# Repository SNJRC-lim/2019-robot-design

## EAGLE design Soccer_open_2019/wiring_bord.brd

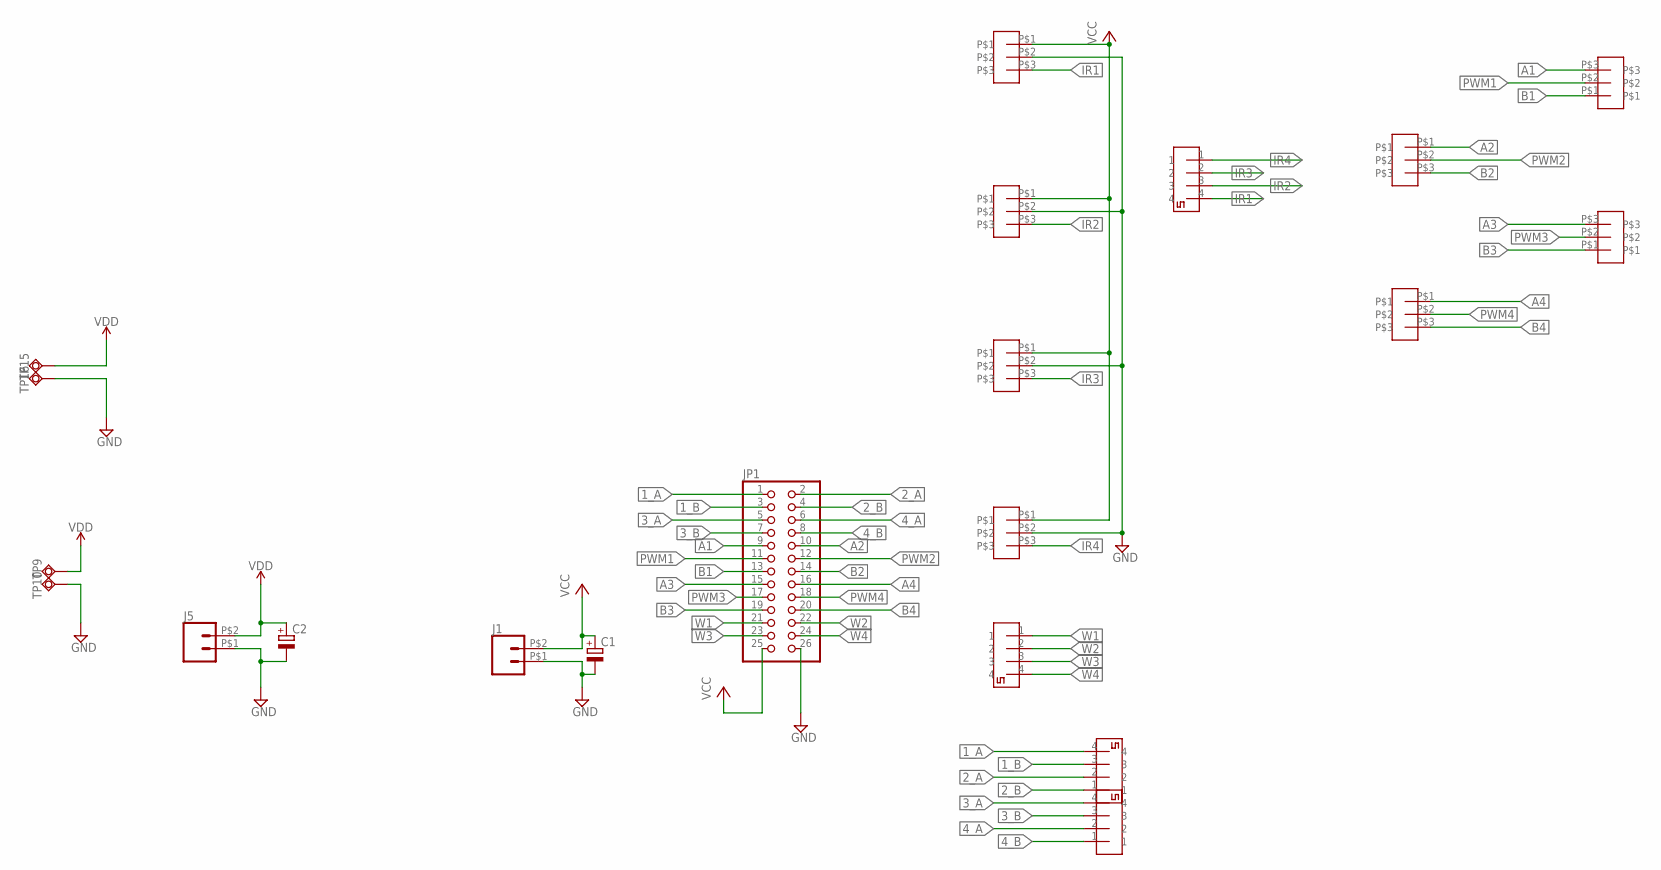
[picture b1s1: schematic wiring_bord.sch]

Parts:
C1, C2: CPOL-EUE2-5; E2-5
CONNECTOR1, CONNECTOR2, CONNECTOR3, CONNECTOR4: 2PIN
IR_DISTANCE1, IR_DISTANCE2, IR_DISTANCE3, IR_DISTANCE4, IR_DISTANCE5, IR_DISTANCE6, IR_DISTANCE7, IR_DISTANCE8: 3PIN
J1, J5: CONN_02PTH2; 1X02_BIG
JP1: PINHD-2X13; 2X13
TP9, TP10: TESTPAD_TPSQPAD1-20; TESTPAD_P1-20
TP15, TP16: TESTPAD_TPSQPAD1-13; TESTPAD_P1-13

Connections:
1_A: CONNECTOR3.4, JP1.1
1_B: CONNECTOR3.3, JP1.3
2_A: CONNECTOR3.2, JP1.2
2_B: CONNECTOR3.1, JP1.4
3_A: CONNECTOR4.4, JP1.5
3_B: CONNECTOR4.3, JP1.7
4_A: CONNECTOR4.2, JP1.6
4_B: CONNECTOR4.1, JP1.8
A1: IR_DISTANCE5.P$3, JP1.9
A2: IR_DISTANCE6.P$1, JP1.10
A3: IR_DISTANCE7.P$3, JP1.15
A4: IR_DISTANCE8.P$1, JP1.16
B1: IR_DISTANCE5.P$1, JP1.13
B2: IR_DISTANCE6.P$3, JP1.14
B3: IR_DISTANCE7.P$1, JP1.19
B4: IR_DISTANCE8.P$3, JP1.20
GND: C1.-, C2.-, IR_DISTANCE1.P$2, IR_DISTANCE2.P$2, IR_DISTANCE3.P$2, IR_DISTANCE4.P$2, J1.P$1 (1), J5.P$1 (1), JP1.26, TP10.TP, TP16.TP
IR1: CONNECTOR1.4, IR_DISTANCE1.P$3
IR2: CONNECTOR1.3, IR_DISTANCE2.P$3
IR3: CONNECTOR1.2, IR_DISTANCE3.P$3
IR4: CONNECTOR1.1, IR_DISTANCE4.P$3
PWM1: IR_DISTANCE5.P$2, JP1.11
PWM2: IR_DISTANCE6.P$2, JP1.12
PWM3: IR_DISTANCE7.P$2, JP1.17
PWM4: IR_DISTANCE8.P$2, JP1.18
VCC: C1.+, IR_DISTANCE1.P$1, IR_DISTANCE2.P$1, IR_DISTANCE3.P$1, IR_DISTANCE4.P$1, J1.P$2 (2), JP1.25
VDD: C2.+, J5.P$2 (2), TP9.TP, TP15.TP
W1: CONNECTOR2.1, JP1.21
W2: CONNECTOR2.2, JP1.22
W3: CONNECTOR2.3, JP1.23
W4: CONNECTOR2.4, JP1.24

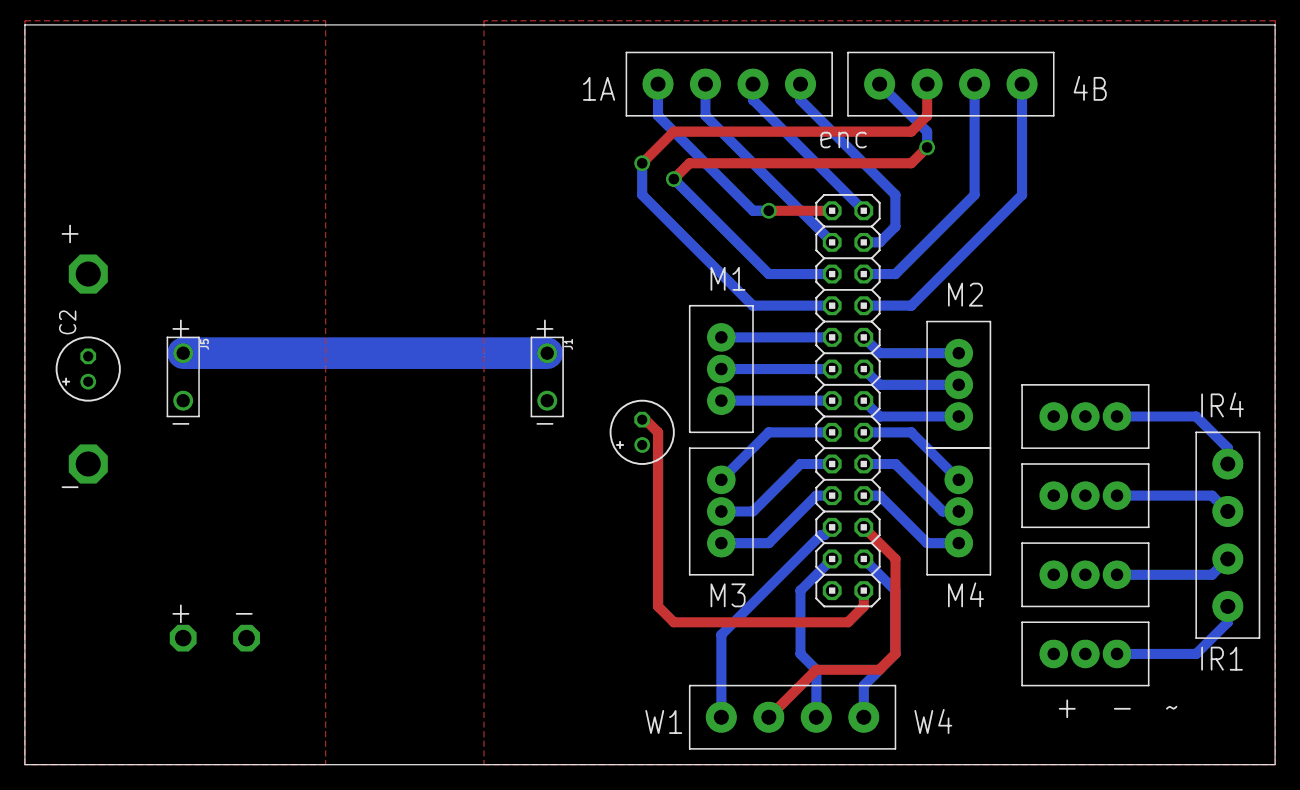
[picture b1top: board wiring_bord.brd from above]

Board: 2 copper layers, 100.3 x 59.4 mm, 21 parts (1 on the bottom side), 31 nets.

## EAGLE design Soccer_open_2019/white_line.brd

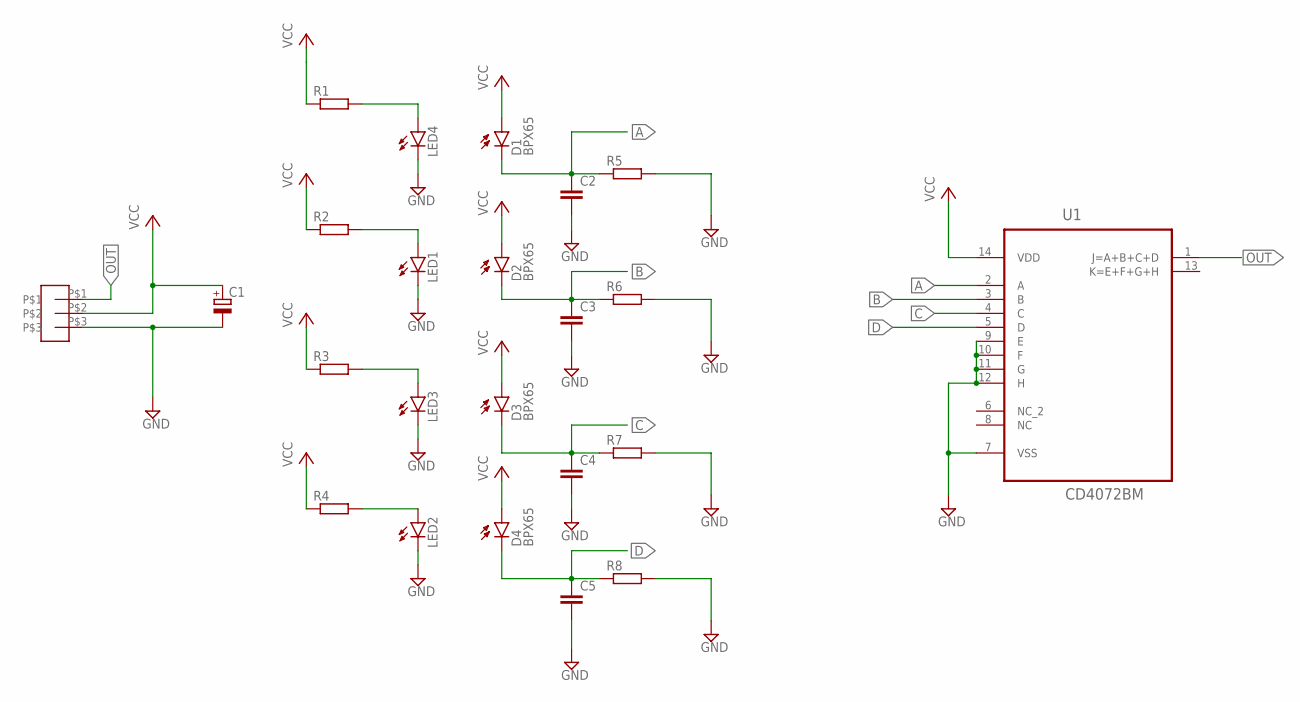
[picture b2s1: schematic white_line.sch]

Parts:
3PIN2: 3PIN
C1: CPOL-EUE2-5; E2-5
C2, C3, C4, C5: C-EU050-024X044; C050-024X044
D1, D2, D3, D4: BPX65
LED1, LED2, LED3, LED4: LED3MM
R1, R2, R3, R4, R5, R6, R7, R8: R-EU_0204/7; 0204/7
U1: CD4072BM; SOIC127P600X175-14N

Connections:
A: C2.1, D1.K (C), R5.1, U1.2 (A)
B: C3.1, D2.K (C), R6.1, U1.3 (B)
C: C4.1, D3.K (C), R7.1, U1.4 (C)
D: C5.1, D4.K (C), R8.1, U1.5 (D)
GND: 3PIN2.P$3, C1.-, C2.2, C3.2, C4.2, C5.2, LED1.K (C), LED2.K (C), LED3.K (C), LED4.K (C), R5.2, R6.2, R7.2, R8.2, U1.7 (VSS), U1.9 (E), U1.10 (F), U1.11 (G), U1.12 (H)
unnamed: LED4.A, R1.2
unnamed: LED1.A, R2.2
unnamed: LED3.A, R3.2
unnamed: LED2.A, R4.2
OUT: 3PIN2.P$1, U1.1 (J=A+B+C+D)
VCC: 3PIN2.P$2, C1.+, D1.A, D2.A, D3.A, D4.A, R1.1, R2.1, R3.1, R4.1, U1.14 (VDD)

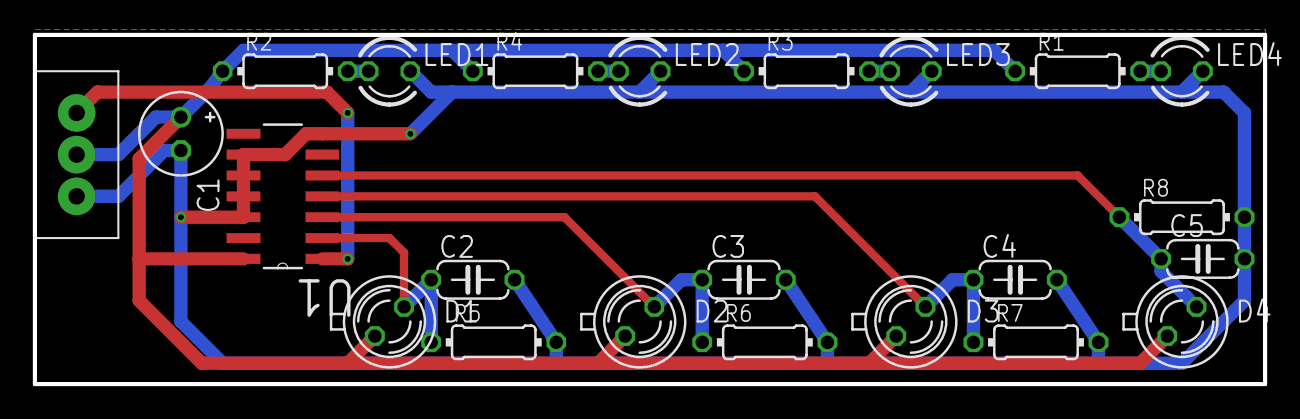
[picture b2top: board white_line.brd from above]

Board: 2 copper layers, 74.9 x 21.3 mm, 23 parts (0 on the bottom side), 11 nets.

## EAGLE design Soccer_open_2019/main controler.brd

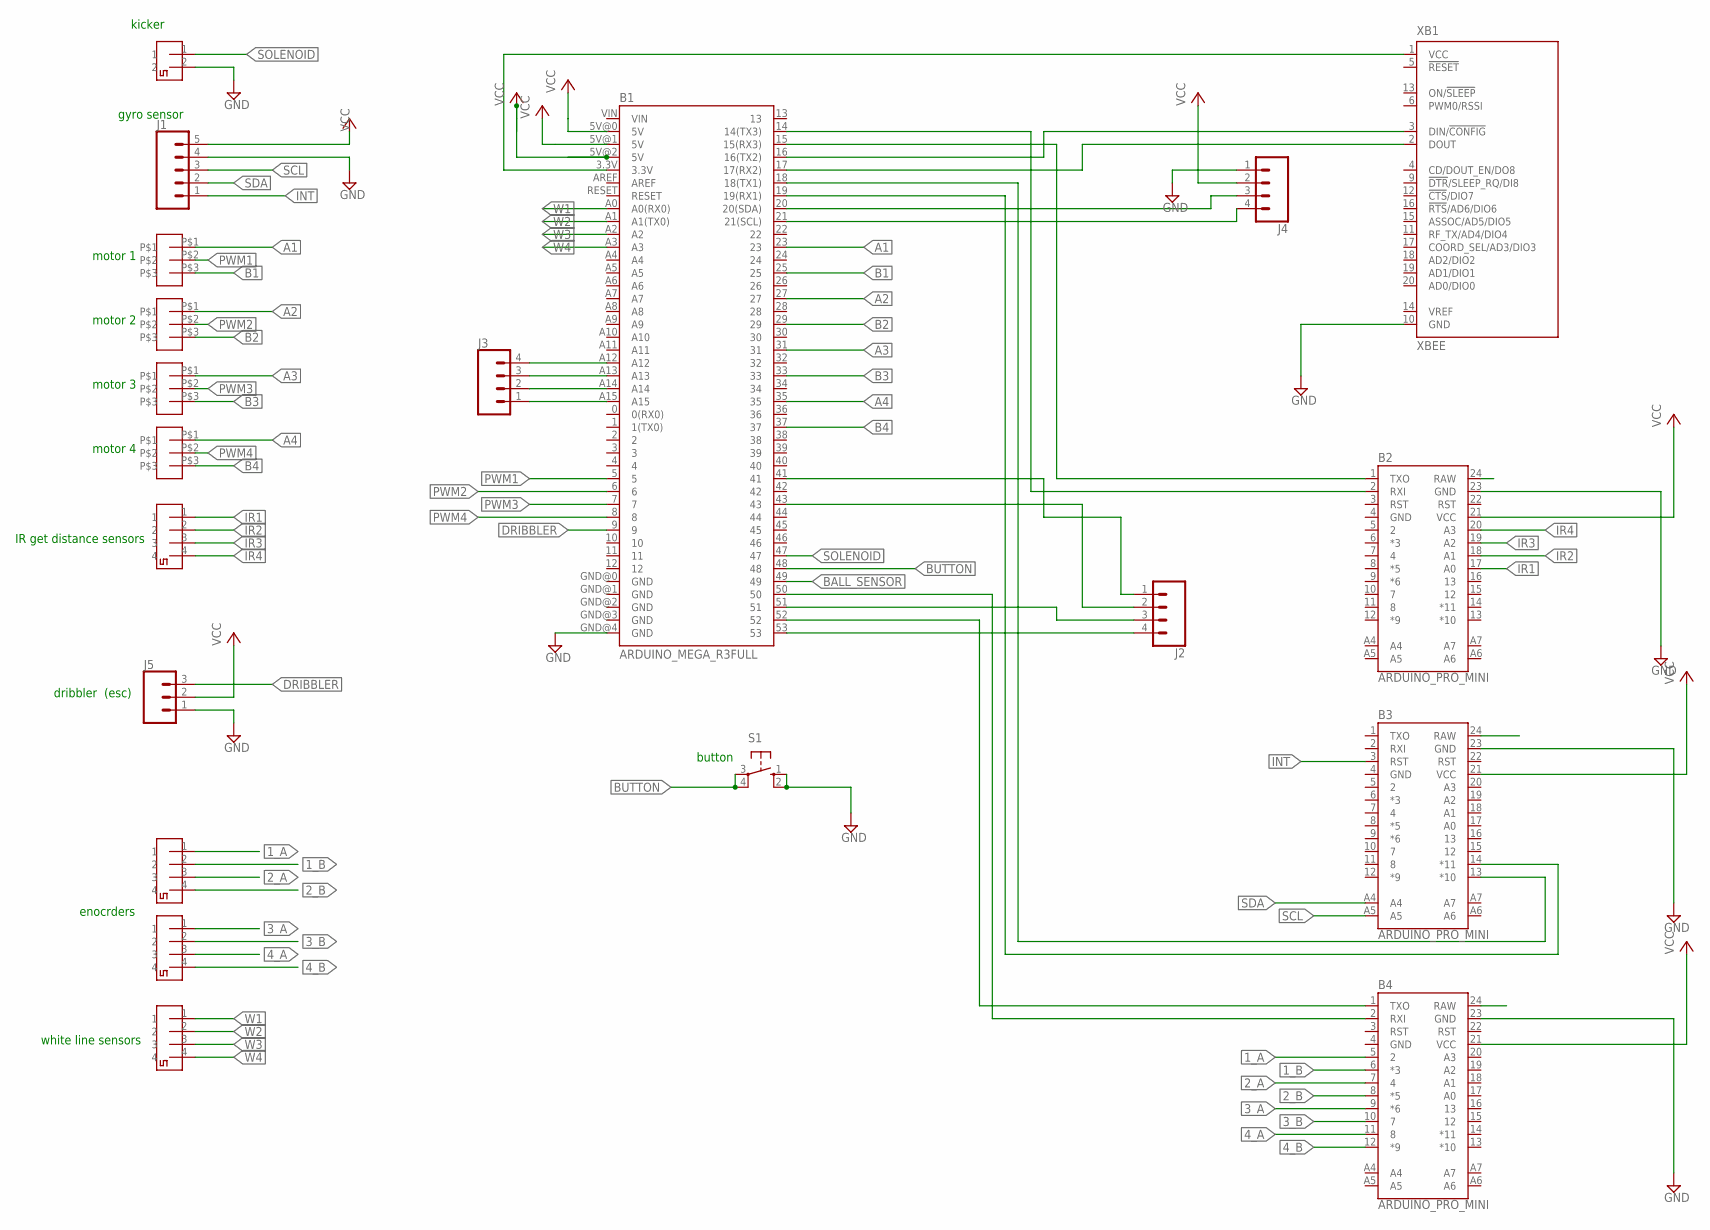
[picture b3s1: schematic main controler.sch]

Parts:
B1: ARDUINO_MEGA_R3FULL; ARDUINO_MEGA
B2, B3, B4: ARDUINO_PRO_MINI
CONNECTOR1: 2PIN
ENCODER1, ENCODER2, ENCODER3, ENCODER4: 2PIN
J1: CONN_05; 1X05
J2, J3, J4: CONN_04; 1X04
J5: CONN_03; 1X03
MOTOR1, MOTOR2, MOTOR3, MOTOR4: 3PIN
S1: 10-XX; B3F-10XX
XB1: XBEE

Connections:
1_A: B4.5 (2), ENCODER2.1
1_B: B4.6 (*3), ENCODER2.2
2_A: B4.7 (4), ENCODER2.3
2_B: B4.8 (*5), ENCODER2.4
3_A: B4.9 (*6), ENCODER1.1
3_B: B4.10 (7), ENCODER1.2
4_A: B4.11 (8), ENCODER1.3
4_B: B4.12 (*9), ENCODER1.4
A1: B1.23, MOTOR1.P$1
A2: B1.27, MOTOR2.P$1
A3: B1.31, MOTOR3.P$1
A4: B1.35, MOTOR4.P$1
B1: B1.25, MOTOR1.P$3
B2: B1.29, MOTOR2.P$3
B3: B1.33, MOTOR3.P$3
B4: B1.37, MOTOR4.P$3
BALL_SENSOR: B1.49
BUTTON: B1.48, S1.3, S1.4 (P1)
DRIBBLER: B1.9, J5.3
GND: B1.GND@4 (GND), B2.4 (GND), B2.23 (GND), B3.4 (GND), B3.23 (GND), B4.4 (GND), B4.23 (GND), CONNECTOR1.2, J1.4, J4.1, J5.1, S1.1 (S), S1.2 (S1), XB1.10 (GND)
INT: B3.3 (RST), J1.1
IR1: B2.17 (A0), ENCODER4.1
IR2: B2.18 (A1), ENCODER4.2
IR3: B2.19 (A2), ENCODER4.3
IR4: B2.20 (A3), ENCODER4.4
unnamed: B1.3.3V, XB1.1 (VCC)
unnamed: B1.16 (16(TX2)), XB1.3 (DIN/!CONFIG)
unnamed: B1.15 (15(RX3)), B2.1 (TXO)
unnamed: B1.14 (14(TX3)), B2.2 (RXI)
unnamed: B1.17 (17(RX2)), XB1.2 (DOUT)
unnamed: B1.19 (19(RX1)), B3.14 (*11)
unnamed: B1.18 (18(TX1)), B3.13 (*10)
unnamed: B1.50, B4.2 (RXI)
unnamed: B1.52, B4.1 (TXO)
unnamed: B1.43, J2.2
unnamed: B1.51, J2.3
unnamed: B1.53, J2.4
unnamed: B1.41, J2.1
unnamed: B1.A15, J3.1
unnamed: B1.A14, J3.2
unnamed: B1.A13, J3.3
unnamed: B1.A12, J3.4
unnamed: B1.21 (21(SCL)), J4.4
unnamed: B1.20 (20(SDA)), J4.3
PWM1: B1.5, MOTOR1.P$2
PWM2: B1.6, MOTOR2.P$2
PWM3: B1.7, MOTOR3.P$2
PWM4: B1.8, MOTOR4.P$2
SCL: B3.A5, J1.3
SDA: B3.A4, J1.2
SOLENOID: B1.47, CONNECTOR1.1
VCC: B1.5V@0 (5V), B1.5V@1 (5V), B1.5V@2 (5V), B2.21 (VCC), B3.21 (VCC), B4.21 (VCC), J1.5, J4.2, J5.2
W1: B1.A0 (A0(RX0)), ENCODER3.1
W2: B1.A1 (A1(TX0)), ENCODER3.2
W3: B1.A2, ENCODER3.3
W4: B1.A3, ENCODER3.4

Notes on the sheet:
kicker
gyro sensor
motor 1
motor 2
motor 3
motor 4
IR get distance sensors
dribbler (esc)
white line sensors
enocrders
button

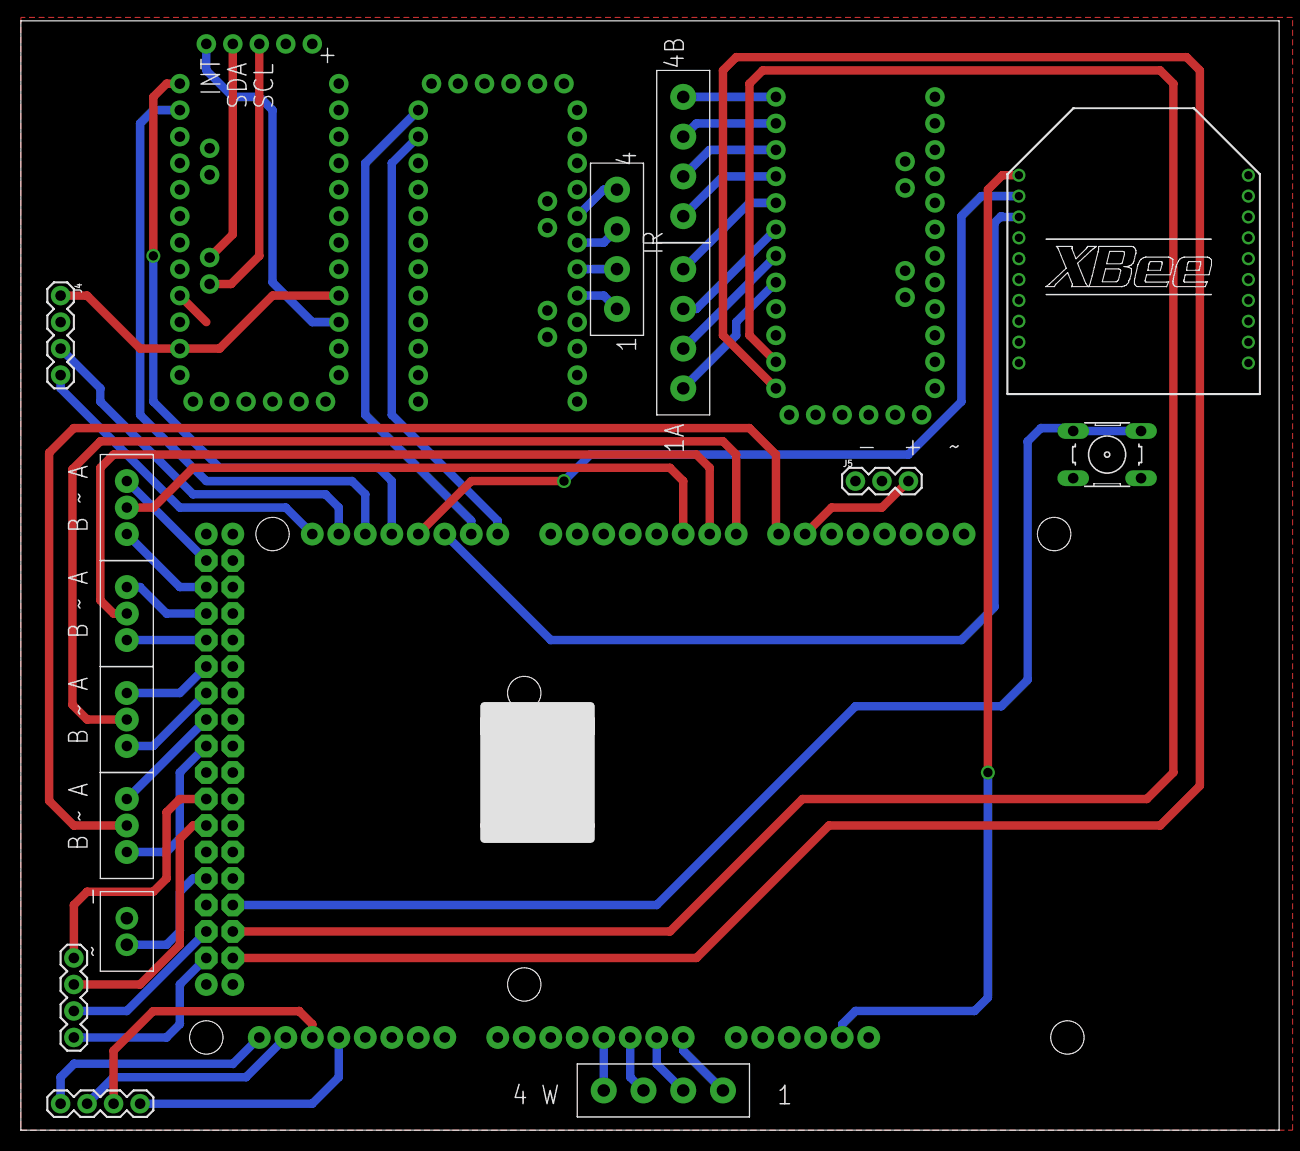
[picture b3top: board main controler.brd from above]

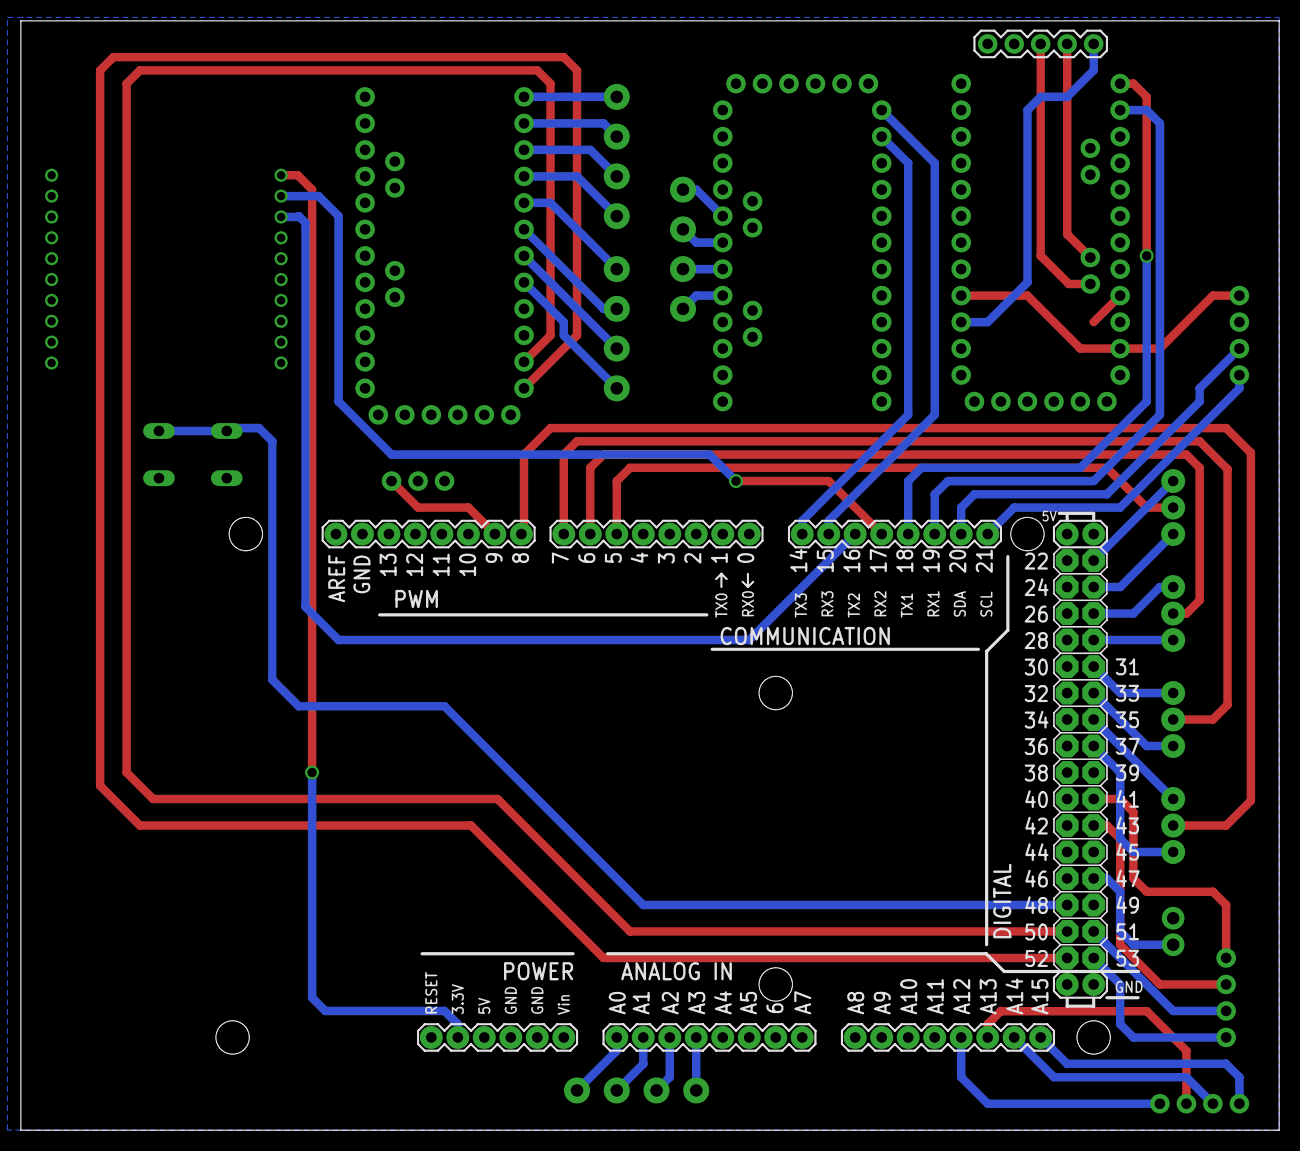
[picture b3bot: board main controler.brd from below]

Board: 2 copper layers, 120.6 x 106.4 mm, 20 parts (3 on the bottom side), 55 nets.

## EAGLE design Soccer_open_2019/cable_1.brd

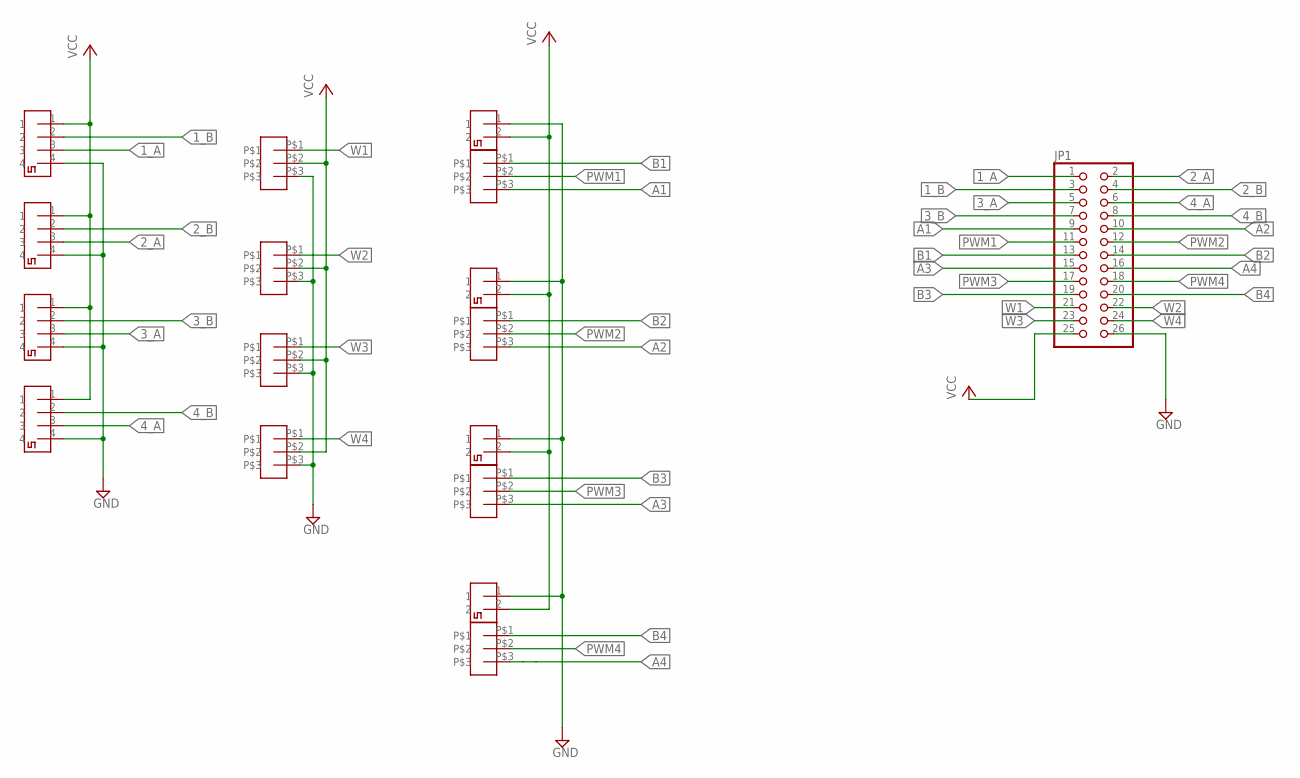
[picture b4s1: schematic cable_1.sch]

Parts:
3PIN1, 3PIN2, 3PIN3, 3PIN4, 3PIN5, 3PIN6, 3PIN7, 3PIN8: 3PIN
CONNECTOR1, CONNECTOR2, CONNECTOR3, CONNECTOR4, CONNECTOR5, CONNECTOR6, CONNECTOR7, CONNECTOR8: 2PIN
JP1: PINHD-2X13; 2X13

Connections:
1_A: CONNECTOR5.3, JP1.1
1_B: CONNECTOR5.2, JP1.3
2_A: CONNECTOR6.3, JP1.2
2_B: CONNECTOR6.2, JP1.4
3_A: CONNECTOR7.3, JP1.5
3_B: CONNECTOR7.2, JP1.7
4_A: CONNECTOR8.3, JP1.6
4_B: CONNECTOR8.2, JP1.8
A1: 3PIN5.P$3, JP1.9
A2: 3PIN6.P$3, JP1.10
A3: 3PIN7.P$3, JP1.15
A4: 3PIN8.P$3, JP1.16
B1: 3PIN5.P$1, JP1.13
B2: 3PIN6.P$1, JP1.14
B3: 3PIN7.P$1, JP1.19
B4: 3PIN8.P$1, JP1.20
GND: 3PIN1.P$3, 3PIN2.P$3, 3PIN3.P$3, 3PIN4.P$3, CONNECTOR1.1, CONNECTOR2.1, CONNECTOR3.1, CONNECTOR4.1, CONNECTOR5.4, CONNECTOR6.4, CONNECTOR7.4, CONNECTOR8.4, JP1.26
PWM1: 3PIN5.P$2, JP1.11
PWM2: 3PIN6.P$2, JP1.12
PWM3: 3PIN7.P$2, JP1.17
PWM4: 3PIN8.P$2, JP1.18
VCC: 3PIN1.P$2, 3PIN2.P$2, 3PIN3.P$2, 3PIN4.P$2, CONNECTOR1.2, CONNECTOR2.2, CONNECTOR3.2, CONNECTOR4.2, CONNECTOR5.1, CONNECTOR6.1, CONNECTOR7.1, CONNECTOR8.1, JP1.25
W1: 3PIN1.P$1, JP1.21
W2: 3PIN2.P$1, JP1.22
W3: 3PIN3.P$1, JP1.23
W4: 3PIN4.P$1, JP1.24

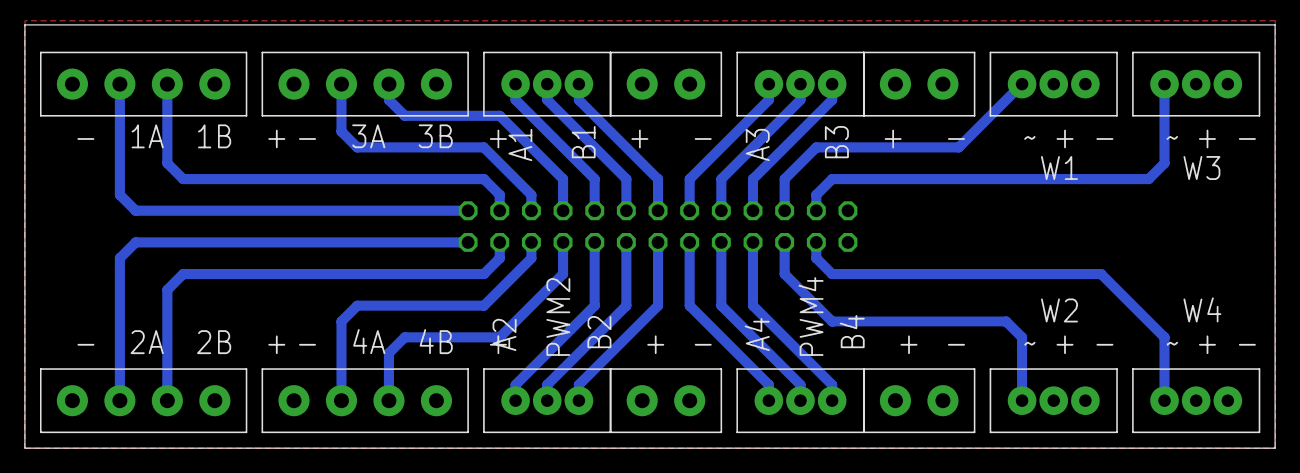
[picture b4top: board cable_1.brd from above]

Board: 2 copper layers, 100.3 x 34.0 mm, 17 parts (1 on the bottom side), 26 nets.

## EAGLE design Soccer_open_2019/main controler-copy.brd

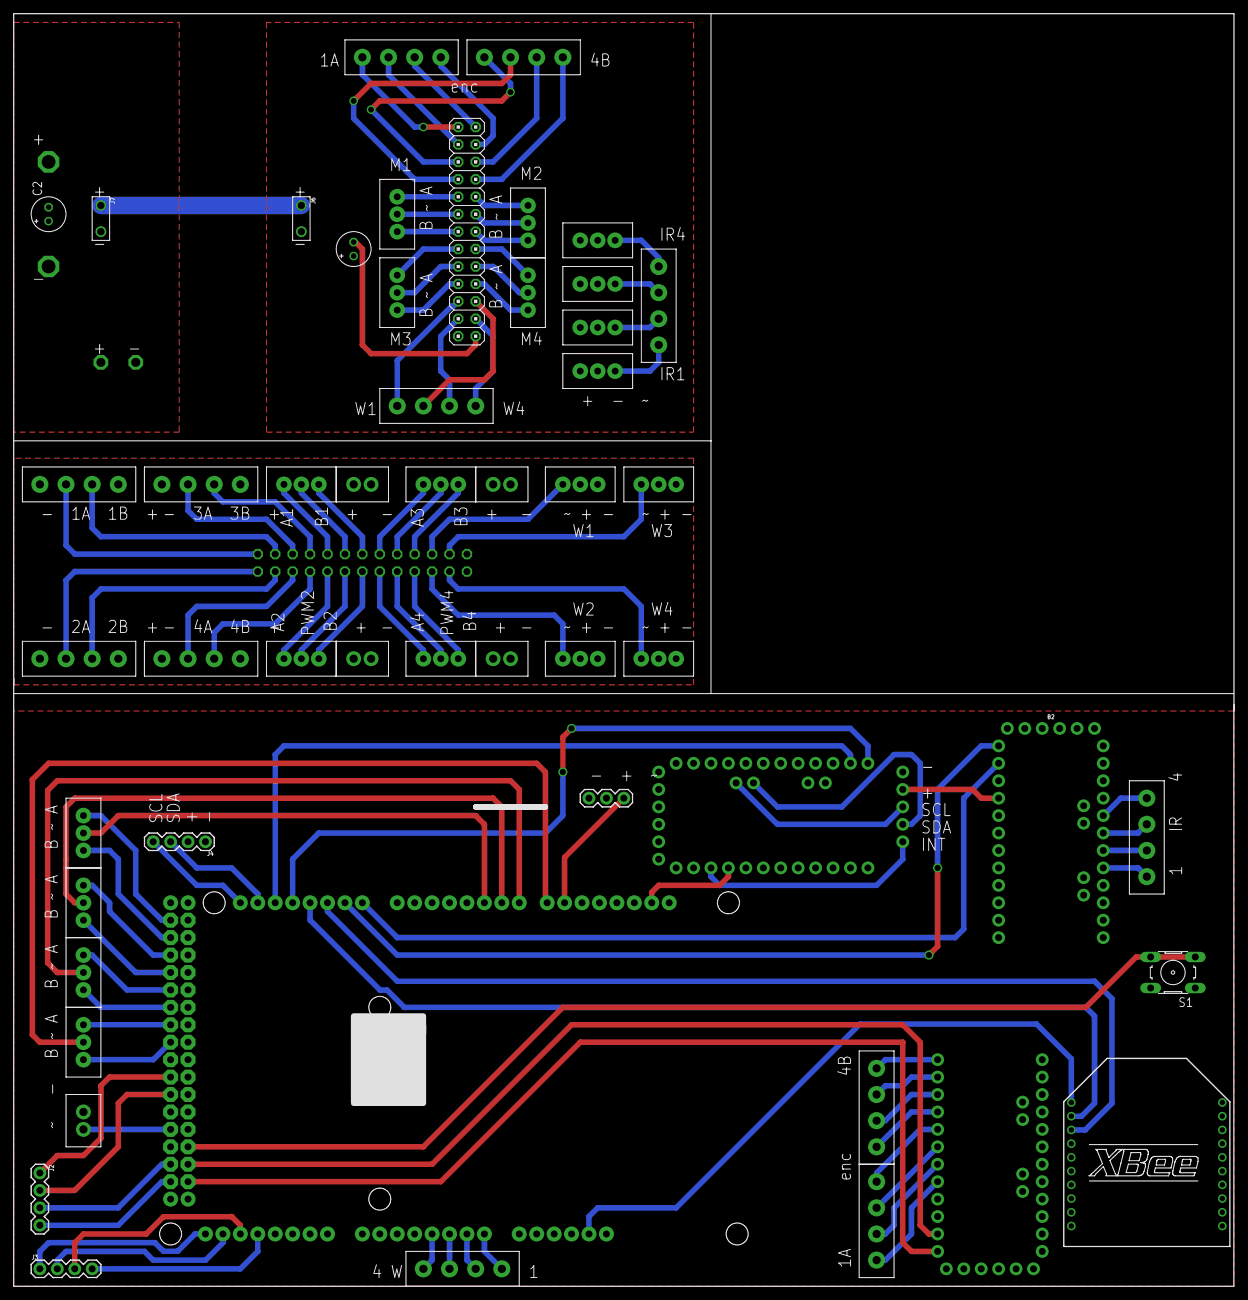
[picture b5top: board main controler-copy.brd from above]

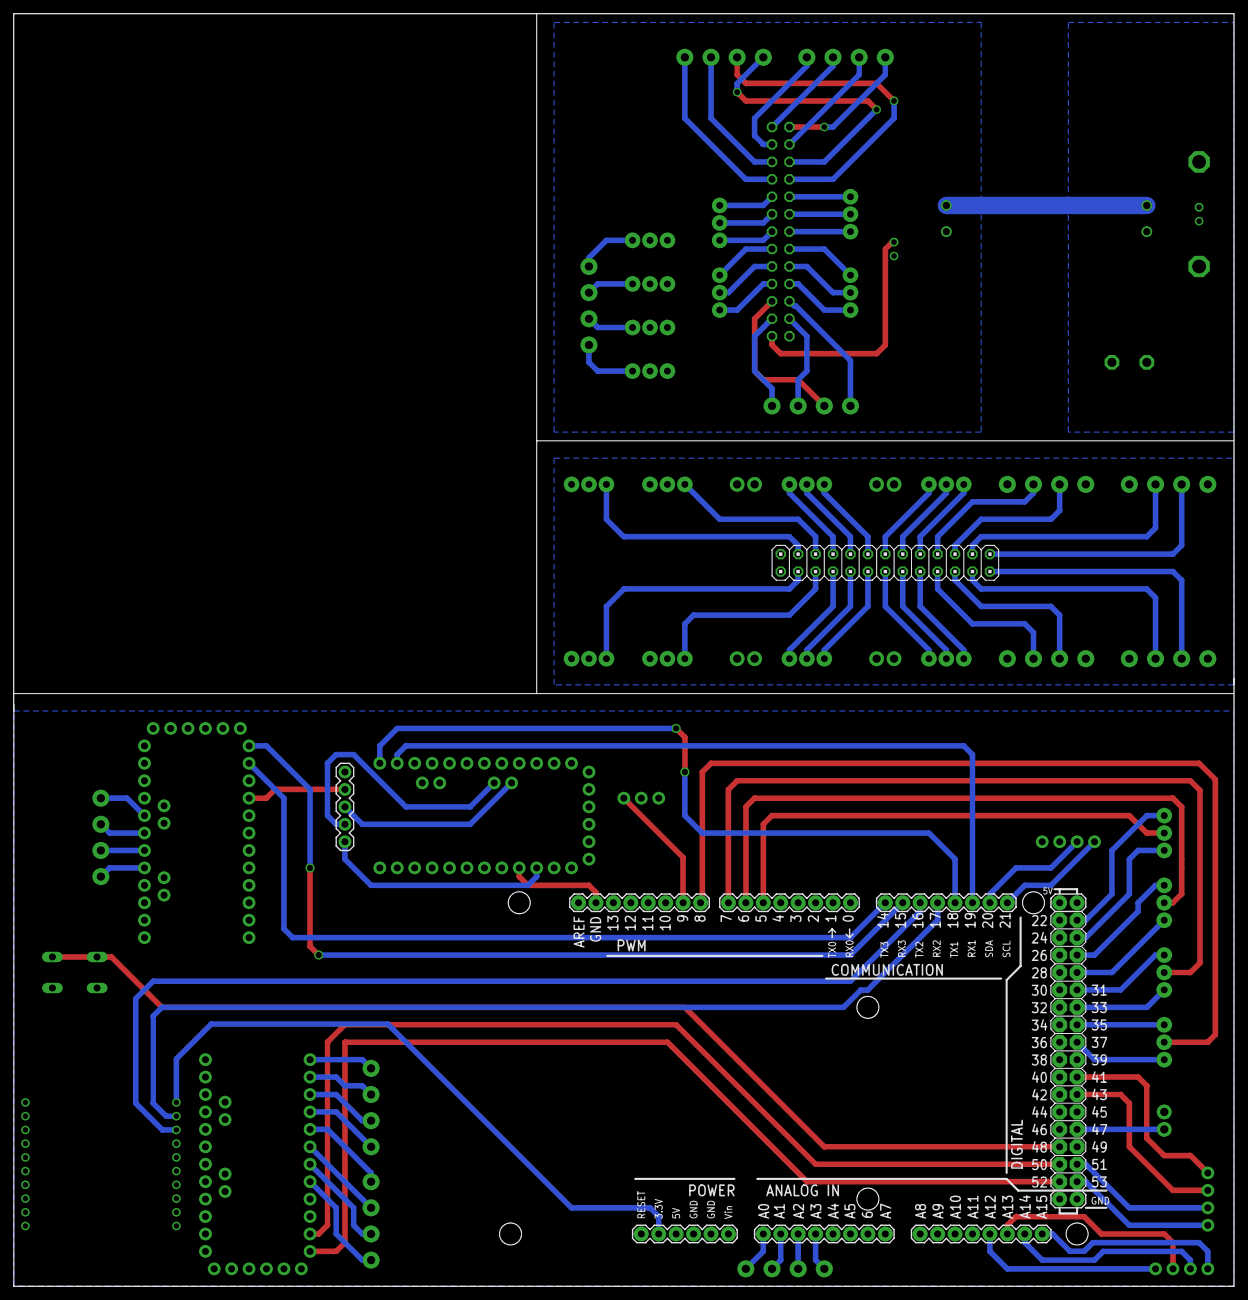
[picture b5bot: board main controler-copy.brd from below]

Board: 2 copper layers, 177.8 x 185.4 mm, 58 parts (5 on the bottom side), 112 nets.

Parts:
3PIN1, 3PIN2, 3PIN3, 3PIN4, 3PIN5, 3PIN6, 3PIN7, 3PIN8: 3PIN
B1: ARDUINO_MEGA_R3FULL; ARDUINO_MEGA
B2, B3, B4: ARDUINO_PRO_MINI
C1, C2: E2-5
CONNECTOR1, CONNECTOR2, CONNECTOR3, CONNECTOR4, CONNECTOR5, CONNECTOR6, CONNECTOR7, CONNECTOR8, CONNECTOR9, CONNECTOR10, CONNECTOR11, CONNECTOR12: 2PIN
ENCODER1, ENCODER2, ENCODER3, ENCODER4: 2PIN
IR_DISTANCE1, IR_DISTANCE2, IR_DISTANCE3, IR_DISTANCE4, IR_DISTANCE5, IR_DISTANCE6, IR_DISTANCE7, IR_DISTANCE8: 3PIN
J1: 1X05
J2, J3, J4: 1X04
J5: 1X03
J6, J7: 1X02_BIG
JP1, JP2: 2X13
MOTOR1, MOTOR2, MOTOR3, MOTOR4: 3PIN
S1: B3F-10XX
SOLENOID: 2PIN
TP9, TP10: TESTPAD_TPSQPAD1-20; TESTPAD_P1-20
TP15, TP16: TESTPAD_TPSQPAD1-13; TESTPAD_P1-13
XB1: XBEE

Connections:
1_A: B4.5, ENCODER2.1
1_A1: CONNECTOR3.4, JP1.1
1_A2: CONNECTOR9.3, JP2.1
1_B: B4.6, ENCODER2.2
1_B1: CONNECTOR3.3, JP1.3
1_B2: CONNECTOR9.2, JP2.3
2_A: B4.7, ENCODER2.3
2_A1: CONNECTOR3.2, JP1.2
2_A2: CONNECTOR10.3, JP2.2
2_B: B4.8, ENCODER2.4
2_B1: CONNECTOR3.1, JP1.4
2_B2: CONNECTOR10.2, JP2.4
3_A: B4.9, ENCODER1.1
3_A1: CONNECTOR4.4, JP1.5
3_A2: CONNECTOR11.3, JP2.5
3_B: B4.10, ENCODER1.2
3_B1: CONNECTOR4.3, JP1.7
3_B2: CONNECTOR11.2, JP2.7
4_A: B4.11, ENCODER1.3
4_A1: CONNECTOR4.2, JP1.6
4_A2: CONNECTOR12.3, JP2.6
4_B: B4.12, ENCODER1.4
4_B1: CONNECTOR4.1, JP1.8
4_B2: CONNECTOR12.2, JP2.8
A1: B1.23, MOTOR1.P$1
A2: B1.27, MOTOR2.P$1
A3: B1.31, MOTOR3.P$1
A4: B1.35, MOTOR4.P$1
A5: IR_DISTANCE7.P$3, JP1.15
A6: IR_DISTANCE8.P$1, JP1.16
A7: IR_DISTANCE6.P$1, JP1.10
A8: IR_DISTANCE5.P$3, JP1.9
A9: 3PIN5.P$3, JP2.9
A10: 3PIN6.P$3, JP2.10
A11: 3PIN7.P$3, JP2.15
A12: 3PIN8.P$3, JP2.16
B1: B1.25, MOTOR1.P$3
B2: B1.29, MOTOR2.P$3
B3: B1.33, MOTOR3.P$3
B4: B1.37, MOTOR4.P$3
B5: IR_DISTANCE8.P$3, JP1.20
B6: IR_DISTANCE7.P$1, JP1.19
B7: IR_DISTANCE6.P$3, JP1.14
B8: IR_DISTANCE5.P$1, JP1.13
B9: 3PIN5.P$1, JP2.13
B10: 3PIN6.P$1, JP2.14
B11: 3PIN7.P$1, JP2.19
B12: 3PIN8.P$1, JP2.20
BUTTON: B1.48, S1.3, S1.4
DRIBBLER: B1.9, J5.3
GND: B1.GND@4, B2.4, B2.23, B3.4, B3.23, B4.4, B4.23, J1.4, J4.1, J5.1, S1.1, S1.2, SOLENOID.2, XB1.10
GND1: C1.-, C2.-, IR_DISTANCE1.P$2, IR_DISTANCE2.P$2, IR_DISTANCE3.P$2, IR_DISTANCE4.P$2, J6.P$1, J7.P$1, JP1.26, TP10.TP, TP16.TP
GND2: 3PIN1.P$3, 3PIN2.P$3, 3PIN3.P$3, 3PIN4.P$3, CONNECTOR5.1, CONNECTOR6.1, CONNECTOR7.1, CONNECTOR8.1, CONNECTOR9.4, CONNECTOR10.4, CONNECTOR11.4, CONNECTOR12.4, JP2.26
INT: B3.3, J1.1
IR1: B2.17, ENCODER4.1
IR2: B2.18, ENCODER4.2
IR3: B2.19, ENCODER4.3
IR4: B2.20, ENCODER4.4
IR5: CONNECTOR1.3, IR_DISTANCE2.P$3
IR6: CONNECTOR1.2, IR_DISTANCE3.P$3
IR7: CONNECTOR1.1, IR_DISTANCE4.P$3
IR8: CONNECTOR1.4, IR_DISTANCE1.P$3
unnamed: B1.3.3V, XB1.1
unnamed: B1.16, XB1.3
unnamed: B1.15, B2.1
unnamed: B1.14, B2.2
unnamed: B1.17, XB1.2
unnamed: B1.19, B3.14
unnamed: B1.18, B3.13
unnamed: B1.50, B4.2
unnamed: B1.52, B4.1
unnamed: B1.43, J2.2
unnamed: B1.51, J2.3
unnamed: B1.53, J2.4
unnamed: B1.41, J2.1
unnamed: B1.A15, J3.1
unnamed: B1.A14, J3.2
unnamed: B1.A13, J3.3
unnamed: B1.A12, J3.4
unnamed: B1.21, J4.4
unnamed: B1.20, J4.3
PWM1: B1.5, MOTOR1.P$2
PWM2: B1.6, MOTOR2.P$2
PWM3: B1.7, MOTOR3.P$2
PWM4: B1.8, MOTOR4.P$2
PWM5: IR_DISTANCE7.P$2, JP1.17
PWM6: IR_DISTANCE8.P$2, JP1.18
PWM7: IR_DISTANCE6.P$2, JP1.12
PWM8: IR_DISTANCE5.P$2, JP1.11
PWM9: 3PIN5.P$2, JP2.11
PWM10: 3PIN6.P$2, JP2.12
PWM11: 3PIN7.P$2, JP2.17
PWM12: 3PIN8.P$2, JP2.18
SCL: B3.A5, J1.3
SDA: B3.A4, J1.2
SOLENOID: B1.47, SOLENOID.1
VCC: B1.5V@1, B1.5V@2, B2.21, B3.21, B4.21, J1.5, J4.2, J5.2
VCC1: C1.+, IR_DISTANCE1.P$1, IR_DISTANCE2.P$1, IR_DISTANCE3.P$1, IR_DISTANCE4.P$1, J6.P$2, JP1.25
VCC2: 3PIN1.P$2, 3PIN2.P$2, 3PIN3.P$2, 3PIN4.P$2, CONNECTOR5.2, CONNECTOR6.2, CONNECTOR7.2, CONNECTOR8.2, CONNECTOR9.1, CONNECTOR10.1, CONNECTOR11.1, CONNECTOR12.1, JP2.25
VDD: C2.+, J7.P$2, TP9.TP, TP15.TP
W1: B1.A0, ENCODER3.1
W2: B1.A1, ENCODER3.2
W3: B1.A2, ENCODER3.3
W4: B1.A3, ENCODER3.4
W5: CONNECTOR2.1, JP1.21
W6: CONNECTOR2.2, JP1.22
W7: CONNECTOR2.4, JP1.24
W8: CONNECTOR2.3, JP1.23
W9: 3PIN1.P$1, JP2.21
W10: 3PIN2.P$1, JP2.22
W11: 3PIN3.P$1, JP2.23
W12: 3PIN4.P$1, JP2.24

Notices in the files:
parts and their libraries:
Arduino: Licensing: Creative Commons ShareAlike 4.0 International - https://creativecommons.org/licenses/by-sa/4.0
